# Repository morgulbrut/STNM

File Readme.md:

#STNM

### Description

Simple instrument built around teensy 3.1

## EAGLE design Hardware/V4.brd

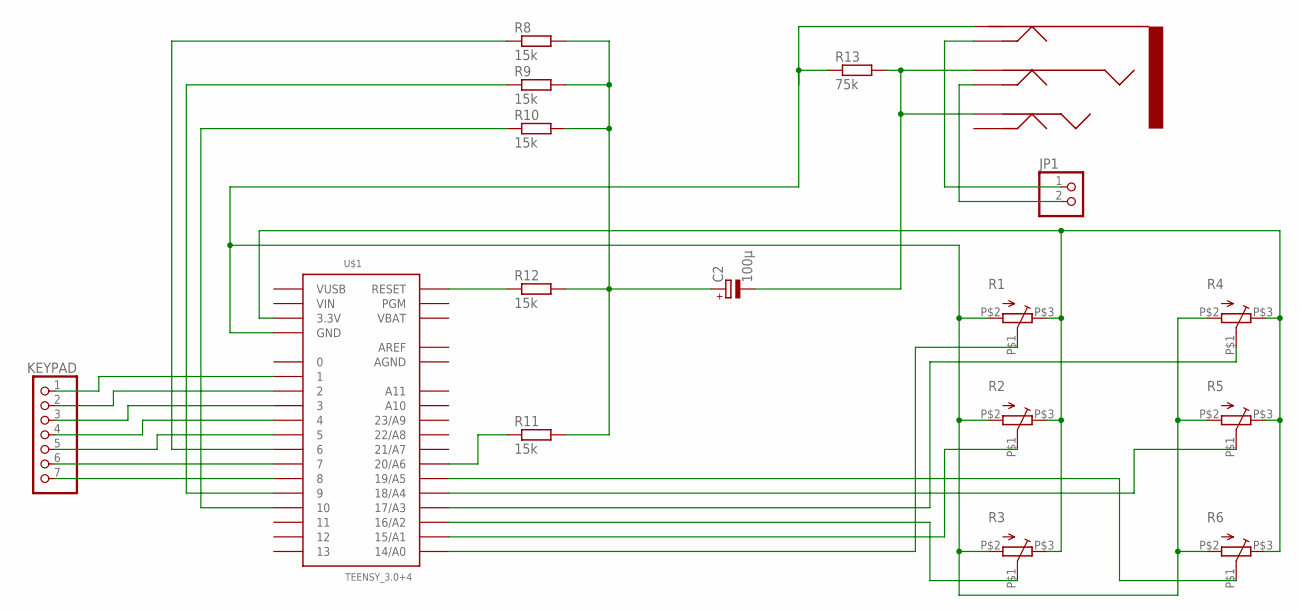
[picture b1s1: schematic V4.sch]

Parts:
C2: 100µ; E2,5-6
JP1: PINHD-1X2; 1X02
KEYPAD: PINHD-1X7; 1X07
R1, R2, R3, R4, R5, R6: STR09K113
R8, R9, R10, R11, R12: 15k; 0309/12
R13: 75k; 0309/12
U$1: TEENSY_3.0+4
U$2: CLIF_3_5; CLIFF_3-5M

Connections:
AGND: U$1.AGND
AREF: U$1.AREF
GND: R1.P$2 (S), R2.P$2 (S), R3.P$2 (S), R4.P$2 (S), R5.P$2 (S), R6.P$2 (S), R13.1, U$1.GND, U$1.GND1 (GND), U$2.GROUND
unnamed: R1.P$1 (W), U$1.14/A0
unnamed: R2.P$1 (W), U$1.15/A1
unnamed: R3.P$1 (W), U$1.16/A2
unnamed: R4.P$1 (W), U$1.17/A3
unnamed: R5.P$1 (W), U$1.18/A4
unnamed: R6.P$1 (W), U$1.19/A5
unnamed: KEYPAD.5, U$1.5
unnamed: R1.P$3 (E), R2.P$3 (E), R3.P$3 (E), R4.P$3 (E), R5.P$3 (E), R6.P$3 (E), U$1.3.3V, U$1.3.3V1 (3.3V)
unnamed: C2.-, R13.2, U$2.RING, U$2.TIP
unnamed: KEYPAD.4, U$1.4
unnamed: KEYPAD.3, U$1.3
unnamed: KEYPAD.2, U$1.2
unnamed: R8.1, U$1.6
unnamed: KEYPAD.6, U$1.7
unnamed: KEYPAD.7, U$1.8
unnamed: KEYPAD.1, U$1.1
unnamed: JP1.1, U$2.GROUND1
unnamed: JP1.2, U$2.RING1
unnamed: R9.1, U$1.9
unnamed: R10.1, U$1.10
unnamed: R12.1, U$1.RESET
unnamed: R11.1, U$1.20/A6
unnamed: C2.+, R8.2, R9.2, R10.2, R11.2, R12.2
VBAT: U$1.VBAT
VIN: U$1.VIN
VUSB: U$1.VUSB

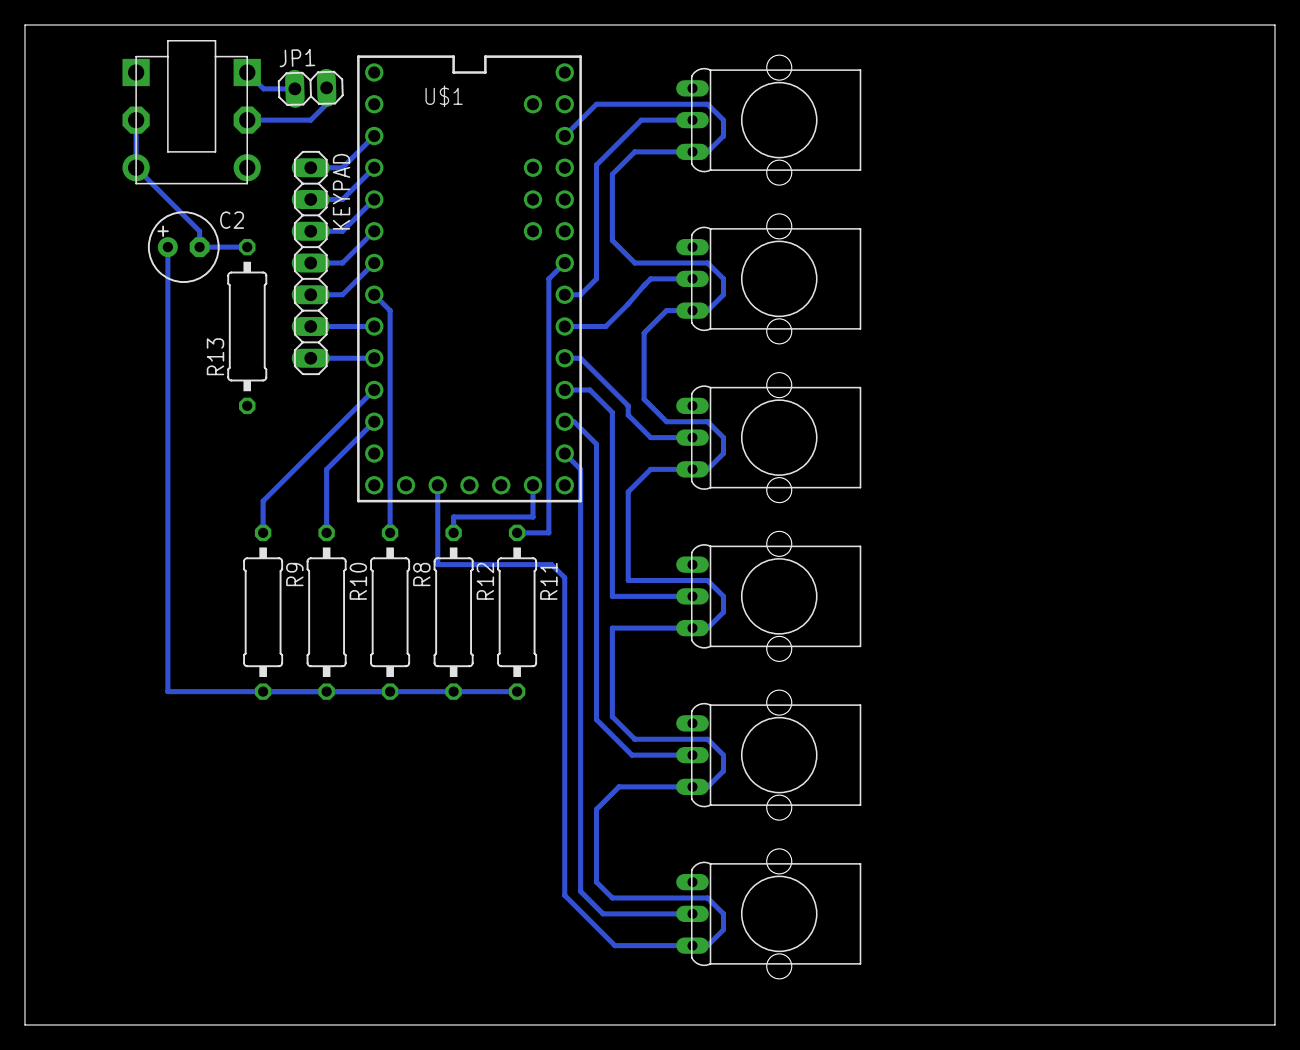
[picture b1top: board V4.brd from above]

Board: 2 copper layers, 100.0 x 80.0 mm, 17 parts (0 on the bottom side), 24 nets.

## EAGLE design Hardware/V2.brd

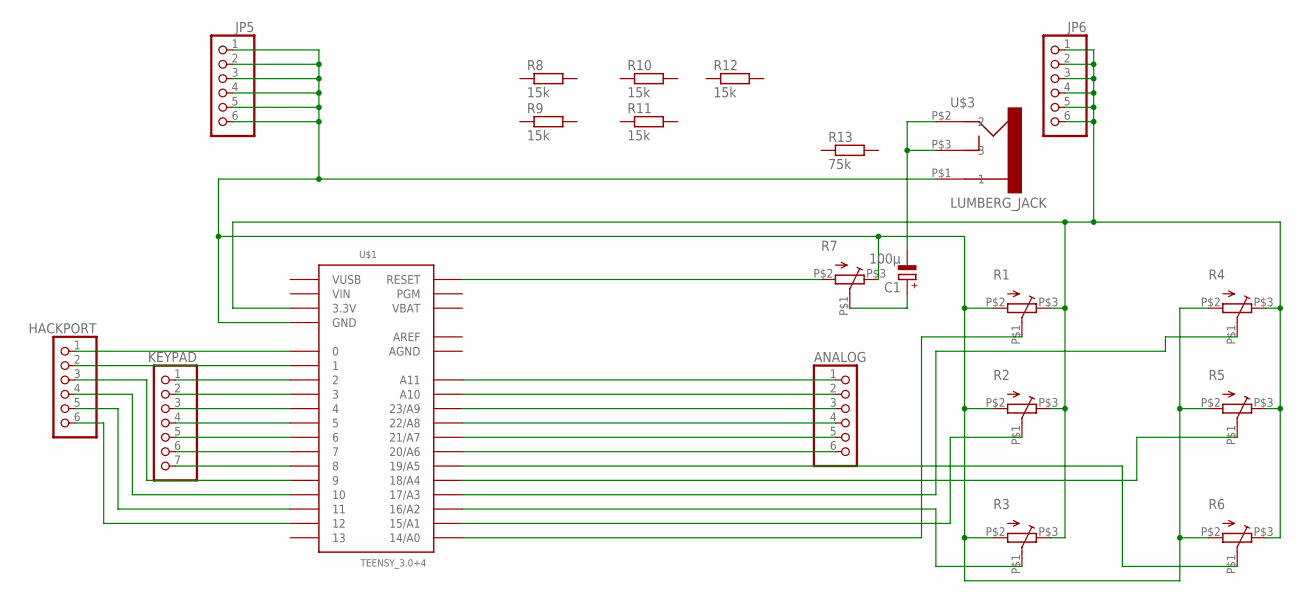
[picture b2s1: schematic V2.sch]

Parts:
ANALOG: PINHD-1X6; 1X06
C1: 100µ; E2,5-6
HACKPORT: PINHD-1X6; 1X06
JP5, JP6: PINHD-1X6; 1X06
KEYPAD: PINHD-1X7; 1X07
R1, R2, R3, R4, R5, R6, R7: STR09K113
R8, R9, R10, R11, R12: 15k; 0309/12
R13: 75k; 0309/12
U$1: TEENSY_3.0+4
U$3: LUMBERG_JACK; JACK_CON

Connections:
AGND: U$1.AGND
AREF: U$1.AREF
GND: JP5.1, JP5.2, JP5.3, JP5.4, JP5.5, JP5.6, R1.P$2 (S), R2.P$2 (S), R3.P$2 (S), R4.P$2 (S), R5.P$2 (S), R6.P$2 (S), R7.P$3 (E), U$1.GND, U$1.GND1 (GND), U$3.P$1 (1)
unnamed: R1.P$1 (W), U$1.14/A0
unnamed: R2.P$1 (W), U$1.15/A1
unnamed: R3.P$1 (W), U$1.16/A2
unnamed: R4.P$1 (W), U$1.17/A3
unnamed: R5.P$1 (W), U$1.18/A4
unnamed: R6.P$1 (W), U$1.19/A5
unnamed: KEYPAD.1, U$1.2
unnamed: JP6.1, JP6.2, JP6.3, JP6.4, JP6.5, JP6.6, R1.P$3 (E), R2.P$3 (E), R3.P$3 (E), R4.P$3 (E), R5.P$3 (E), R6.P$3 (E), U$1.3.3V, U$1.3.3V1 (3.3V)
unnamed: C1.-, U$3.P$2 (2), U$3.P$3 (3)
unnamed: KEYPAD.2, U$1.3
unnamed: KEYPAD.3, U$1.4
unnamed: KEYPAD.4, U$1.5
unnamed: KEYPAD.5, U$1.6
unnamed: KEYPAD.6, U$1.7
unnamed: KEYPAD.7, U$1.8
unnamed: ANALOG.1, U$1.A11
unnamed: ANALOG.2, U$1.A10
unnamed: ANALOG.3, U$1.23/A9
unnamed: ANALOG.4, U$1.22/A8
unnamed: HACKPORT.1, U$1.0
unnamed: HACKPORT.2, U$1.1
unnamed: HACKPORT.3, U$1.9
unnamed: HACKPORT.4, U$1.10
unnamed: HACKPORT.5, U$1.11
unnamed: HACKPORT.6, U$1.12
unnamed: R7.P$2 (S), U$1.RESET
unnamed: C1.+, R7.P$1 (W)
unnamed: ANALOG.5, U$1.21/A7
unnamed: ANALOG.6, U$1.20/A6
VBAT: U$1.VBAT
VIN: U$1.VIN
VUSB: U$1.VUSB

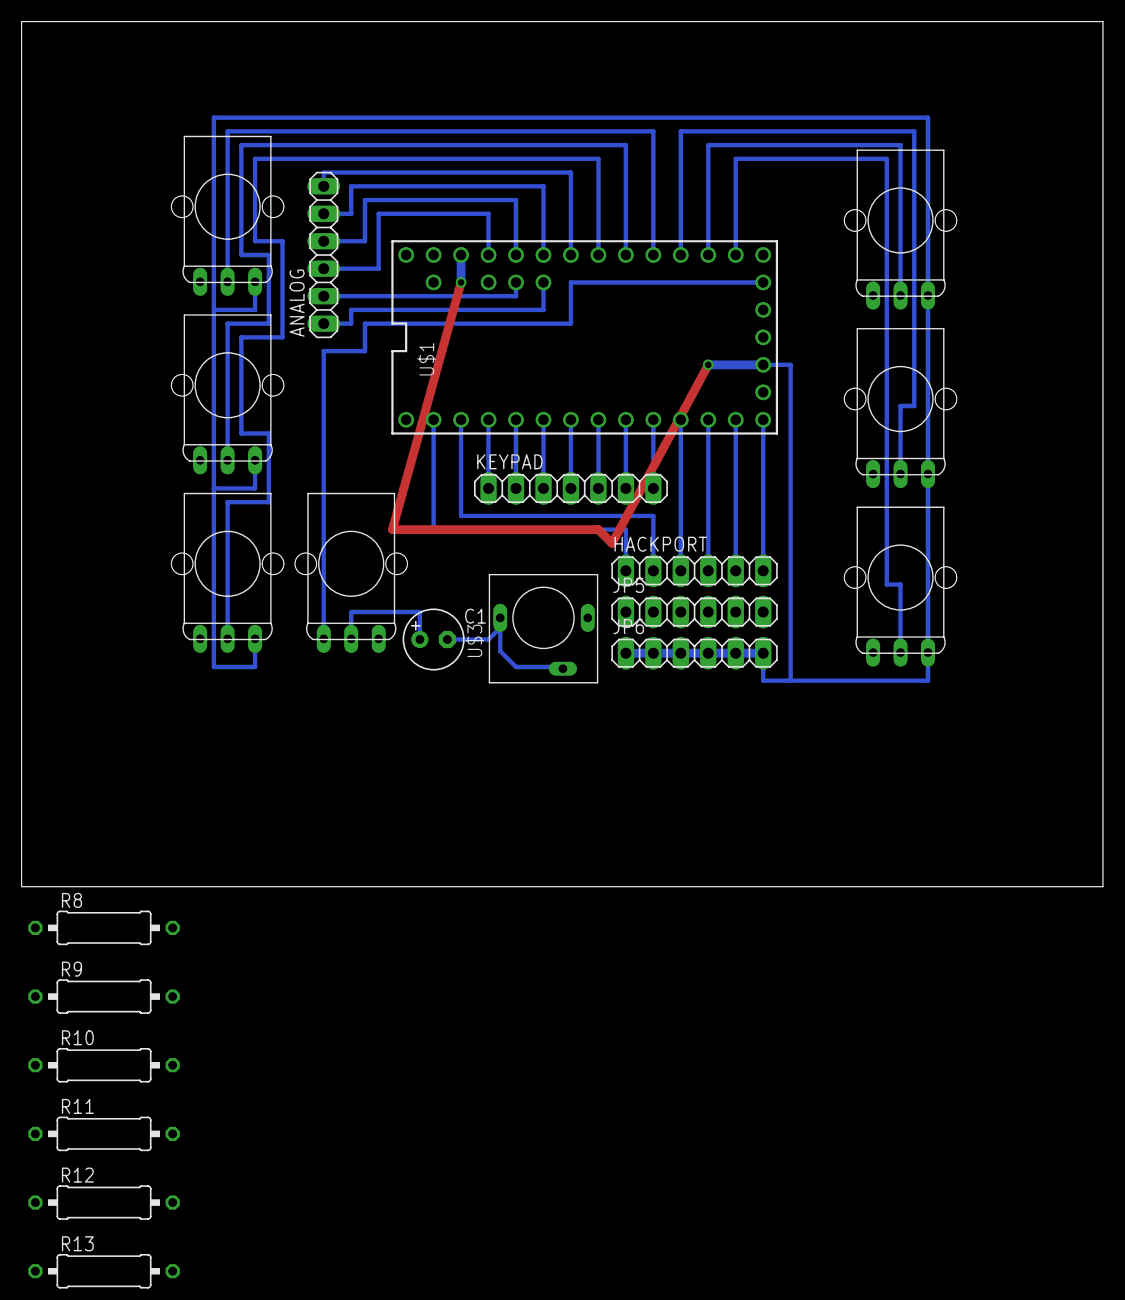
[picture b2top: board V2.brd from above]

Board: 2 copper layers, 100.0 x 80.0 mm, 21 parts (0 on the bottom side), 30 nets.

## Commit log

2014-12-29 :space_invader: Added .gitattributes & .gitignore files
2014-12-29 Inital release
2014-12-29 Inital commit
2014-12-30 Reorganised dirs
2014-12-30 Dirs reorganized
2014-12-31 Intial Commit
2015-01-02 New Example / New hardware version
2015-01-13 Updated gitignore
2015-01-13 Hardware Update
2015-01-22 Hardware update / MIDI Sample updates
